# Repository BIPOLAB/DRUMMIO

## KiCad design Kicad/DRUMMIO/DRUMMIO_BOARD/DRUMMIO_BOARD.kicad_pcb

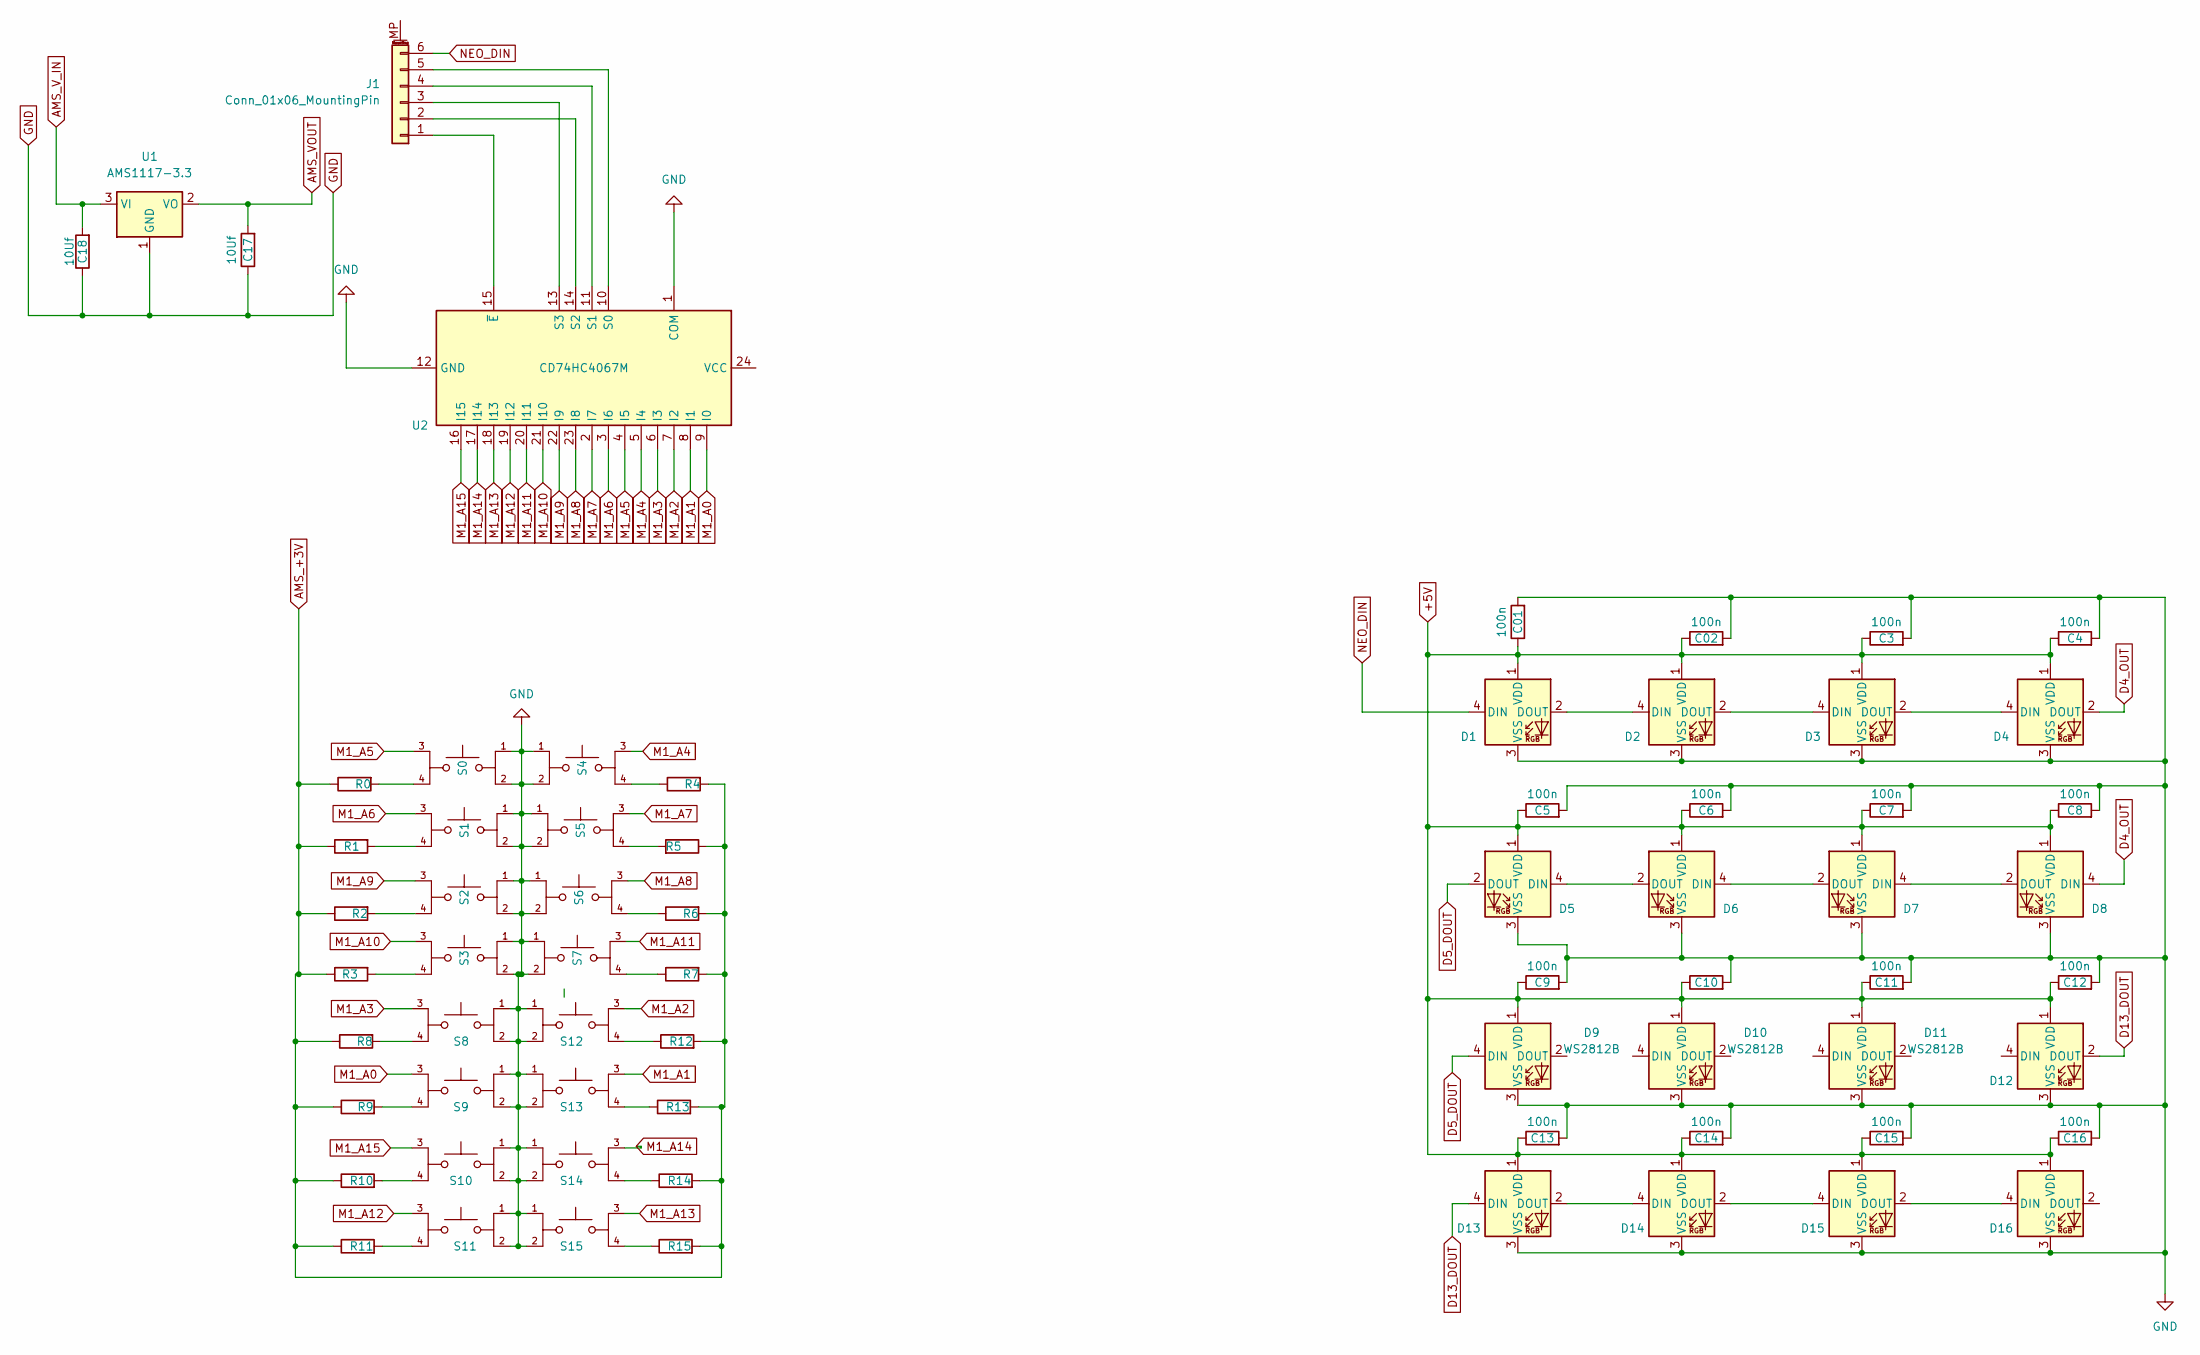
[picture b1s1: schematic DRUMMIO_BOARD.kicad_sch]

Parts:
C01, C02, C3, C4, C5, C6, C7, C8, C9, C10, C11, C12, C13, C14, C15, C16: 100n; C_0805_2012Metric
C17, C18: 10Uf; C_0805_2012Metric
D1, D2, D3, D4, D5, D6, D7, D8, D9, D10, D11, D12, D13, D14, D15, D16: WS2812B; LED_WS2812B_PLCC4_5.0x5.0mm_P3.2mm
J1: Conn_01x06_MountingPin; PinHeader_1x06_P2.00mm_Horizontal
R0, R1, R2, R3, R4, R5, R6, R7, R8, R9, R10, R11, R12, R13, R14, R15: R; R_0805_2012Metric_Pad1.20x1.40mm_HandSolder
S0, S1, S2, S3, S4, S5, S6, S7, S8, S9, S10, S11, S12, S13, S14, S15: TL1100F160Q; SW_TL1100F160Q; PARTREV D
U1: AMS1117-3.3; SOT-223-3_TabPin2
U2: CD74HC4067M; SOIC-24W_7.5x15.4mm_P1.27mm

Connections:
+5V: C01.1, C02.1, C3.1, C4.1, C5.1, C6.1, C7.1, C8.1, C9.1, C10.1, C11.1, C12.1, C13.1, C14.1, C15.1, C16.1, D1.1 (VDD), D2.1 (VDD), D3.1 (VDD), D4.1 (VDD), D5.1 (VDD), D6.1 (VDD), D7.1 (VDD), D8.1 (VDD), D9.1 (VDD), D10.1 (VDD), D11.1 (VDD), D12.1 (VDD), D13.1 (VDD), D14.1 (VDD), D15.1 (VDD), D16.1 (VDD)
AMS_V_IN: C18.2, U1.3 (VI)
D4_OUT: D4.2 (DOUT), D8.4 (DIN)
D5_DOUT: D5.2 (DOUT), D9.4 (DIN)
D13_DOUT: D12.2 (DOUT), D13.4 (DIN)
GND: C01.2, C02.2, C3.2, C4.2, C5.2, C6.2, C7.2, C8.2, C9.2, C10.2, C11.2, C12.2, C13.2, C14.2, C15.2, C16.2, C17.1, C18.1, D1.3 (VSS), D2.3 (VSS), D3.3 (VSS), D4.3 (VSS), D5.3 (VSS), D6.3 (VSS), D7.3 (VSS), D8.3 (VSS), D9.3 (VSS), D10.3 (VSS), D11.3 (VSS), D12.3 (VSS), D13.3 (VSS), D14.3 (VSS), D15.3 (VSS), D16.3 (VSS), S0.2, S1.1, S1.2, S2.1, S2.2, S3.1, S3.2, S4.1, S4.2, S5.1, S5.2, S6.1, S6.2, S7.1, S7.2, S8.1, S8.2, S9.1, S9.2, S10.1, S10.2, S11.1, S11.2, S12.1, S12.2, S13.1, S13.2, S14.1, S14.2, S15.1, S15.2, U1.1 (GND), U2.1 (COM), U2.12 (GND)
M1_A0: S9.3, U2.9 (I0)
M1_A1: S13.3, U2.8 (I1)
M1_A2: S12.3, U2.7 (I2)
M1_A3: S8.3, U2.6 (I3)
M1_A4: S4.3, U2.5 (I4)
M1_A5: S0.3, U2.4 (I5); also elsewhere on the board
M1_A6: S1.3, U2.3 (I6); also elsewhere on the board
M1_A7: S5.3, U2.2 (I7); also elsewhere on the board
M1_A8: S6.3, U2.23 (I8)
M1_A9: S2.3, U2.22 (I9); also elsewhere on the board
M1_A10: S3.3, U2.21 (I10)
M1_A11: S7.3, U2.20 (I11)
M1_A12: S11.3, U2.19 (I12)
M1_A13: S15.3, U2.18 (I13)
M1_A14: S14.3, U2.17 (I14)
M1_A15: S10.3, U2.16 (I15)
NEO_DIN: D1.4 (DIN), J1.6
unnamed: D1.2 (DOUT), D2.4 (DIN)
unnamed: D2.2 (DOUT), D3.4 (DIN)
unnamed: D3.2 (DOUT), D4.4 (DIN)
unnamed: D5.4 (DIN), D6.2 (DOUT)
unnamed: D6.4 (DIN), D7.2 (DOUT)
unnamed: D7.4 (DIN), D8.2 (DOUT)
unnamed: D13.2 (DOUT), D14.4 (DIN)
unnamed: D14.2 (DOUT), D15.4 (DIN)
unnamed: D15.2 (DOUT), D16.4 (DIN)
unnamed: J1.1, U2.15 (~E)
unnamed: J1.2, U2.14 (S2)
unnamed: J1.3, U2.13 (S3)
unnamed: J1.4, U2.11 (S1)
unnamed: J1.5, U2.10 (S0)
unnamed: R0.2, S0.4
unnamed: R1.2, S1.4
unnamed: R2.2, S2.4
unnamed: R3.2, S3.4
unnamed: R4.1, S4.4
unnamed: R5.2, S5.4
unnamed: R6.1, S6.4
unnamed: R7.1, S7.4
unnamed: R8.2, S8.4
unnamed: R9.2, S9.4
unnamed: R10.2, S10.4
unnamed: R11.2, S11.4
unnamed: R12.1, S12.4
unnamed: R13.1, S13.4
unnamed: R14.1, S14.4
unnamed: R15.1, S15.4

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
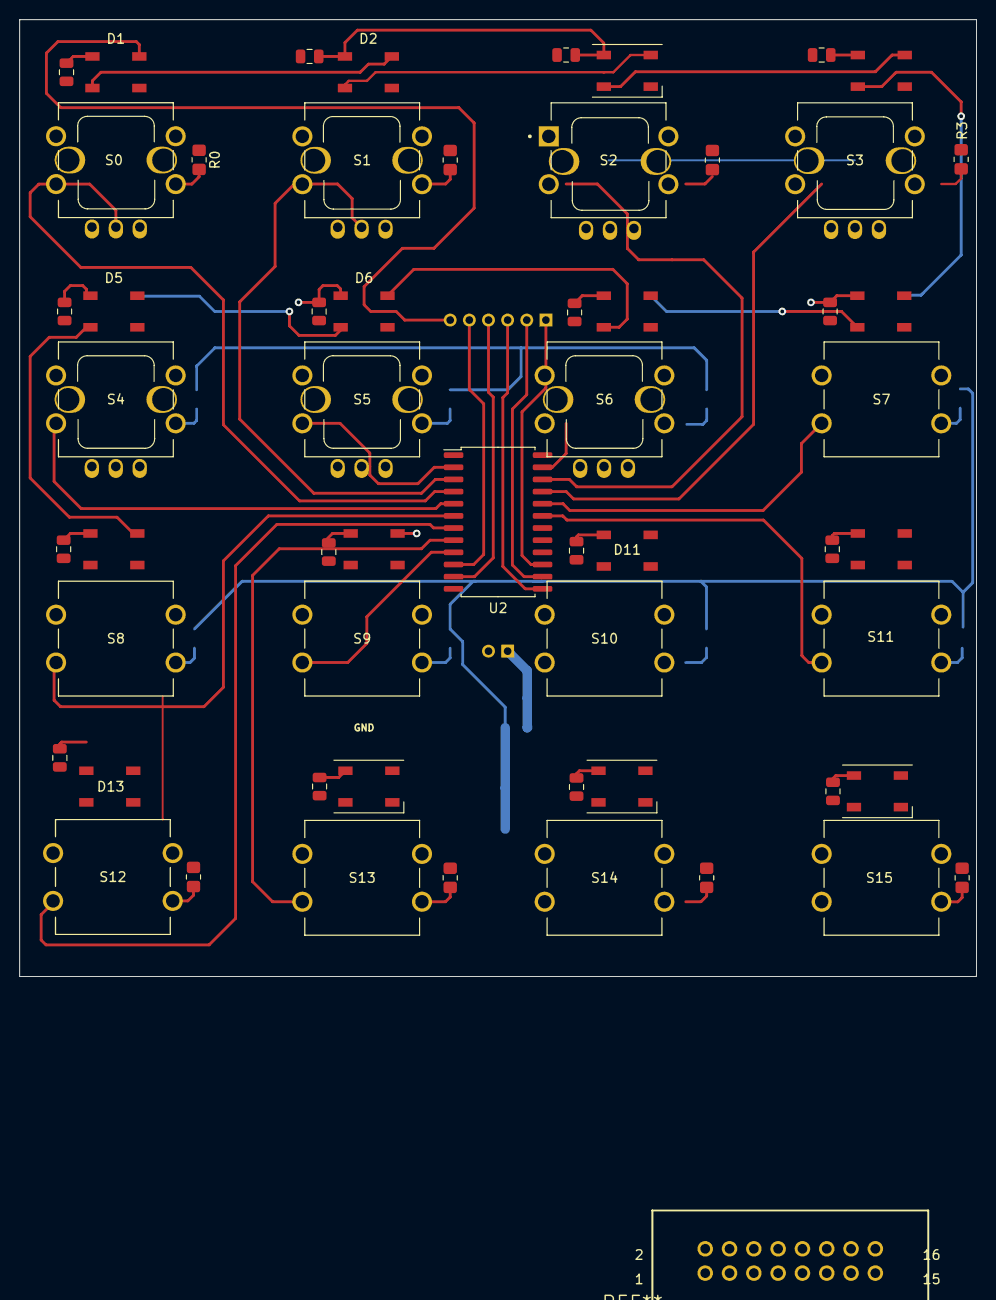
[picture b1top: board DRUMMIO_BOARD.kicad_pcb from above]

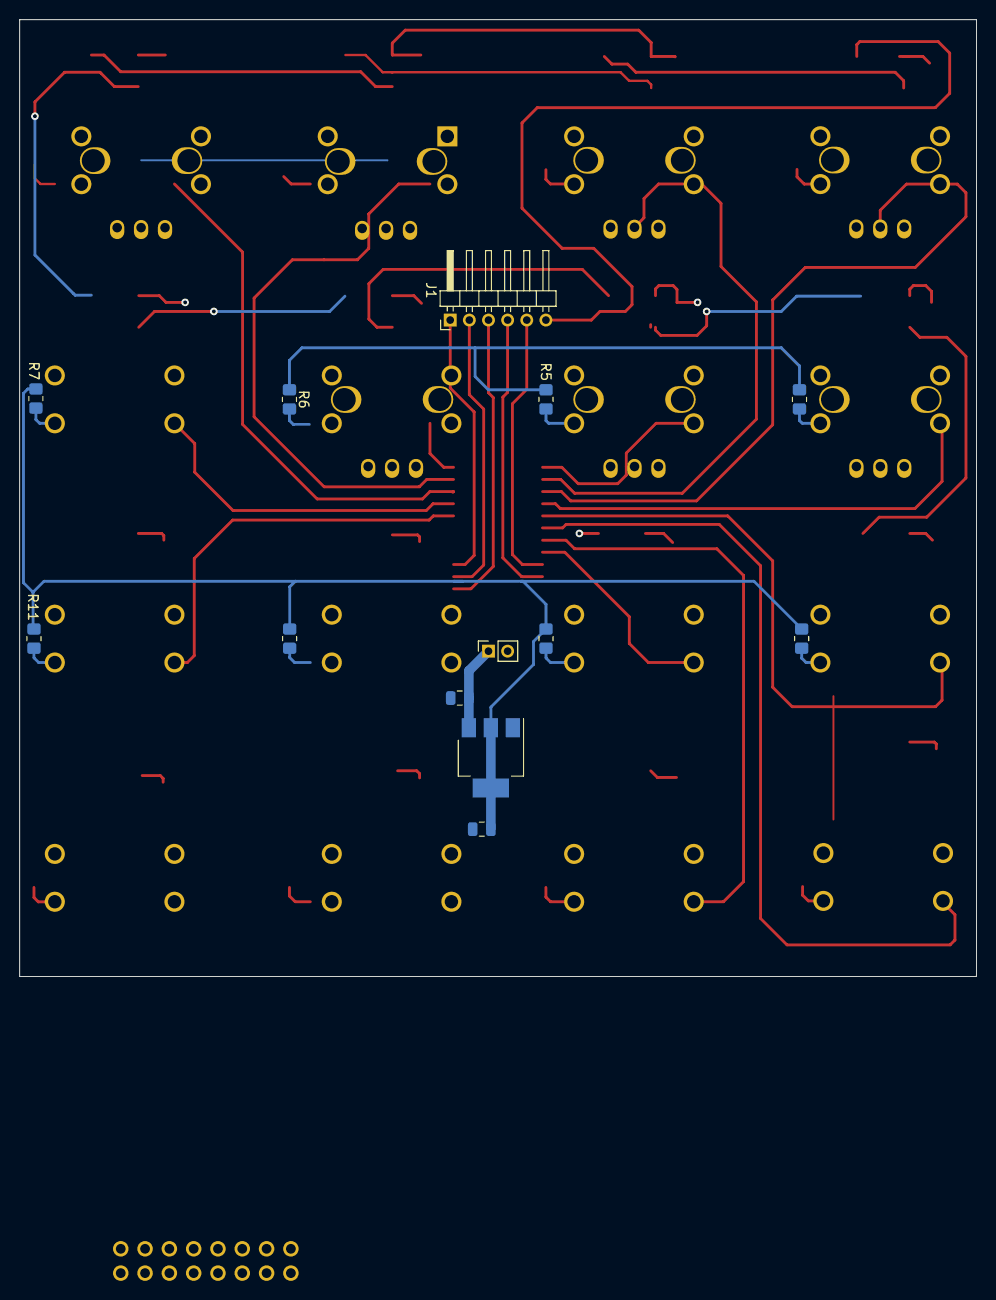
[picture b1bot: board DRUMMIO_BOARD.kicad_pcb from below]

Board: 2 copper layers, 100.0 x 100.0 mm, 76 parts (12 on the bottom side), 55 nets.

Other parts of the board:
UI1010, UI1010#2, UI1010#3, UI1010#4, UI1010#5, UI1010#6, UI1010#7: P090S-04F20BR10K (NF); Potentiometer_Alps_RK09L_Single_Vertical

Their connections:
M1_A5: UI1010#4.2; also elsewhere on the board
M1_A6: UI1010#2.2, UI1010#3.2, UI1010#6.2; also elsewhere on the board
M1_A7: UI1010.2; also elsewhere on the board
M1_A9: UI1010#7.2; also elsewhere on the board

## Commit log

2017-08-24 DRUMMIO
2017-08-25 new
    new
2017-08-26 RRUMIO
    RUMMIO
2022-12-04 Vectores
2022-12-04 Program_update
    First upload for arduino program
2023-10-31 New Branch Developer_Leo
2023-10-31 Kicad Files
2023-10-31 Kicad
2023-10-31 Update Proyect Files
2023-10-31 gitignore
2023-10-31 BT and USB Proyect
2023-10-31 INDEX
2024-03-14 first init
2024-03-14 pryecto parte 3
